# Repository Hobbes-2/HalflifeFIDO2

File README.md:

GOBIKEY
(NOT a Yubikey)

This is for week 5 of Hackclub Half Life, and its a fairly simple (?) key thingy. It consists of USB A connection, a nRF52840 QIAA chip, two buttons, two lights, and some GPIO pins for testing purposes. It is not only for passwords and 2FA (although that was the original purpose), and should double as a devboard kinda thing if i did it right. Without further adeu, my (please please dont slime me for my bad wiring) designs:

Despite it being a simple board (for some ig), it took a lot of mental brainpower for me to complete this, and im not sure if it even works properly (try at own risk lol). It was inspired in part by this (https://docs.nordicsemi.com/r/bundle/ug_nrf52840_dongle/page/ug/nrf52840_dongle/kit_hw_content.html), and yubikeys in general.

To install the firmware, for now just look at this (https://docs.zephyrproject.org/latest/services/authentication/fido2/index.html), im not done with the firmware yet.

# Bill of Materials (BOM)

| Part | Quantity | Unit Price (USD) | Total (USD) | Vendor |
|---|---:|---:|---:|---|
| Button | 2 | $0.54 | $1.08 | [DigiKey](https://www.digikey.com/en/products/detail/würth-elektronik/434133025816/9950810?s=N4IgTCBcDaICwGY4EYEIAxgKwA5kDYQBdAXyA) |
| LED | 2 | $0.19 | $0.38 | [DigiKey](https://www.digikey.com/en/products/detail/würth-elektronik/150060VS55040/8557182) |
| 1k Resistor | 2 | $0.10 | $0.20 | [DigiKey](https://www.digikey.com/en/products/detail/vishay-dale/CRCW06031K00FKEA/1174668) |
| 10k Resistor | 1 | $0.10 | $0.10 | [DigiKey](https://www.digikey.com/en/products/detail/vishay-dale/CRCW060310K0FKEA/1174782) |
| nRF52840 Chip | 1 | $8.81 | $8.81 | [DigiKey](https://www.digikey.com/en/products/detail/nordic-semiconductor-asa/NRF52840-QIAA-R/7725407) |
| PCB | 1 | $10.70 | $10.70 | [JLCPCB](https://cart.jlcpcb.com/shopcart/cart/) |

---

## Cost Summary

| Description | Cost (USD) |
|---|---:|
| Component Subtotal | $10.57 |
| PCB Cost | $10.70 |
| **Grand Total** | **$21.27** |

(PCB cost accounts for shipping, hopefully if i get all my grants at once shipping will be a one time thing)

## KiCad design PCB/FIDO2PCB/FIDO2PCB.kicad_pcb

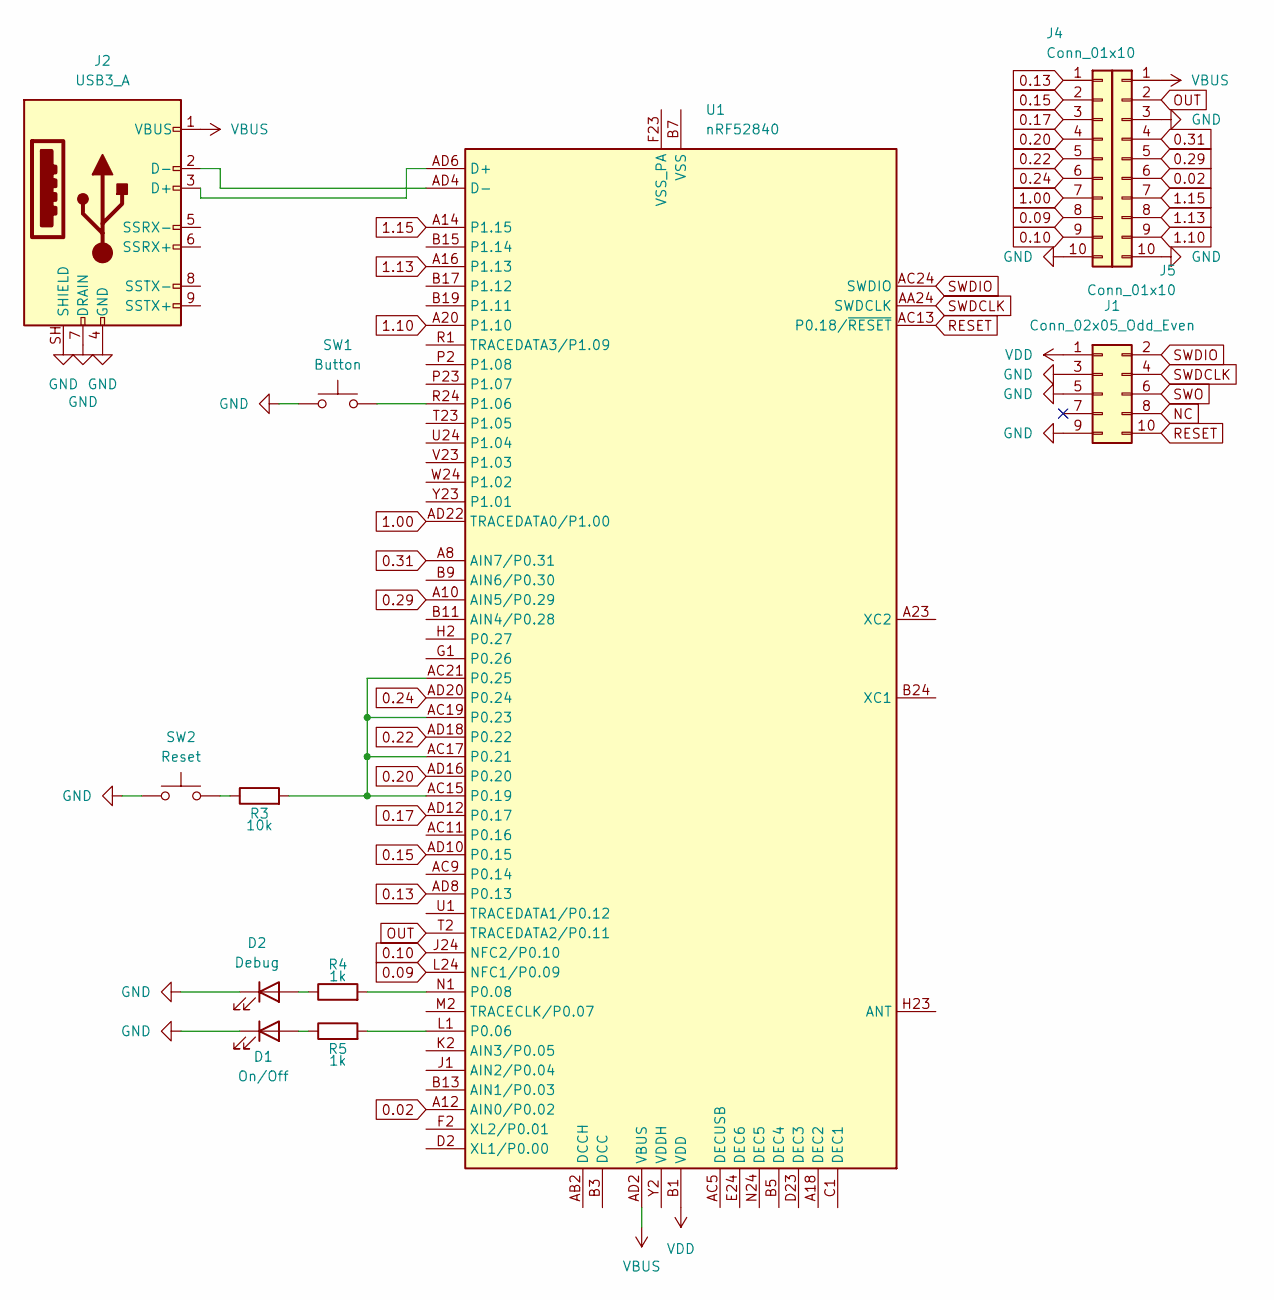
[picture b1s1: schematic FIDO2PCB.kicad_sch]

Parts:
D1: On/Off; LED_0603_1608Metric
D2: Debug; LED_0603_1608Metric
J1: Conn_02x05_Odd_Even; Tag-Connect_TC2050-IDC-FP_2x05_P1.27mm_Vertical
J2: USB3_A; USB_A_PCB_Edge_receptacle
J4, J5: Conn_01x10; PinHeader_1x10_P2.54mm_Vertical
R3: 10k; R_0603_1608Metric
R4, R5: 1k; R_0603_1608Metric
SW1: Button; SW_Push_1P1T_NO_Vertical_Wuerth_434133025816
SW2: Reset; SW_Push_1P1T_NO_Vertical_Wuerth_434133025816
U1: nRF52840; Nordic_AQFN-73-1EP_7x7mm_P0.5mm

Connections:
0.02: J5.6, U1.A12 (AIN0/P0.02)
0.09: J4.8, U1.L24 (NFC1/P0.09)
0.10: J4.9, U1.J24 (NFC2/P0.10)
0.13: J4.1, U1.AD8 (P0.13)
0.15: J4.2, U1.AD10 (P0.15)
0.17: J4.3, U1.AD12 (P0.17)
0.20: J4.4, U1.AD16 (P0.20)
0.22: J4.5, U1.AD18 (P0.22)
0.24: J4.6, U1.AD20 (P0.24)
0.29: J5.5, U1.A10 (AIN5/P0.29)
0.31: J5.4, U1.A8 (AIN7/P0.31)
1.00: J4.7, U1.AD22 (TRACEDATA0/P1.00)
1.10: J5.9, U1.A20 (P1.10)
1.13: J5.8, U1.A16 (P1.13)
1.15: J5.7, U1.A14 (P1.15)
GND: D1.1 (K), D2.1 (K), J1.3, J1.5, J1.9, J2.4 (GND), J2.7 (DRAIN), J2.SH (SHIELD), J4.10, J5.3, J5.10, SW1.1, SW2.1
NC: J1.8
unnamed: D1.2 (A), R5.1
unnamed: D2.2 (A), R4.1
unnamed: J2.3 (D+), U1.AD6 (D+)
unnamed: J2.2 (D-), U1.AD4 (D-)
unnamed: R3.1, SW2.2
unnamed: R5.2, U1.L1 (P0.06)
unnamed: R4.2, U1.N1 (P0.08)
unnamed: R3.2, U1.AC15 (P0.19), U1.AC17 (P0.21), U1.AC19 (P0.23), U1.AC21 (P0.25)
unnamed: SW1.2, U1.R24 (P1.06)
unnamed: U1.B7 (VSS), U1.EP (VSS)
OUT: J5.2, U1.T2 (TRACEDATA2/P0.11)
RESET: J1.10, U1.AC13 (P0.18/~RESET)
SWDCLK: J1.4, U1.AA24 (SWDCLK)
SWDIO: J1.2, U1.AC24 (SWDIO)
SWO: J1.6
VBUS: J2.1 (VBUS), J5.1, U1.AD2 (VBUS)
VDD: J1.1, U1.A22 (VDD), U1.AD14 (VDD), U1.AD23 (VDD), U1.B1 (VDD), U1.W1 (VDD)

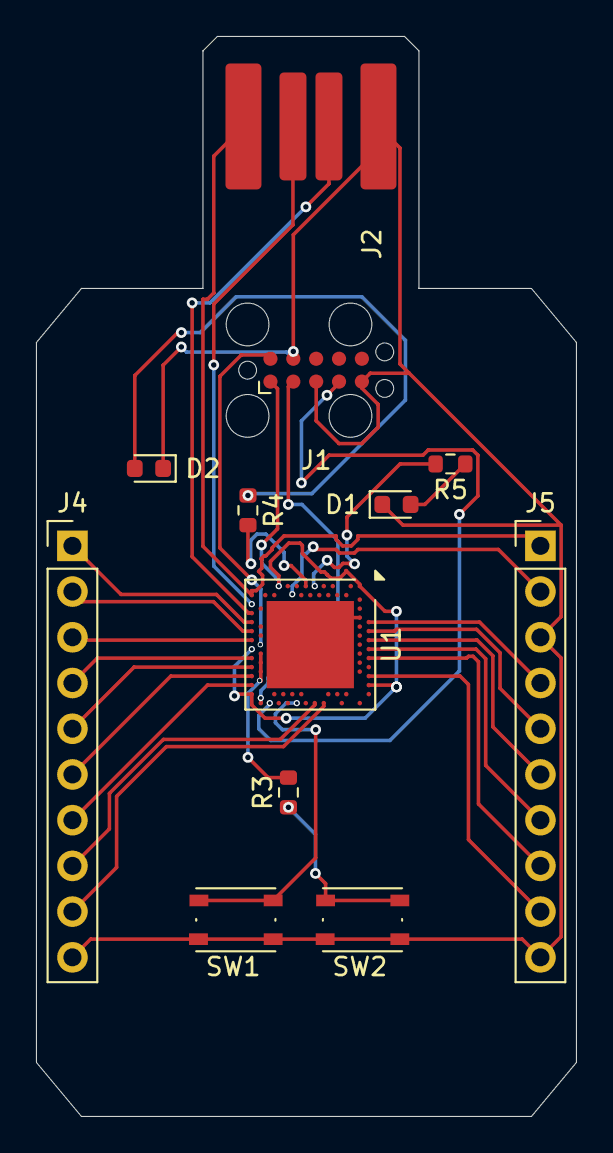
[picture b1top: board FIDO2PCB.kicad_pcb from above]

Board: 2 copper layers, 30.0 x 60.0 mm, 12 parts (0 on the bottom side), 32 nets.
